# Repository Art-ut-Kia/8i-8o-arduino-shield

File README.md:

# 8i-8o-arduino-shield
Arduino Schield / Reads 8 push-button switches &amp; Drives 8 LED's

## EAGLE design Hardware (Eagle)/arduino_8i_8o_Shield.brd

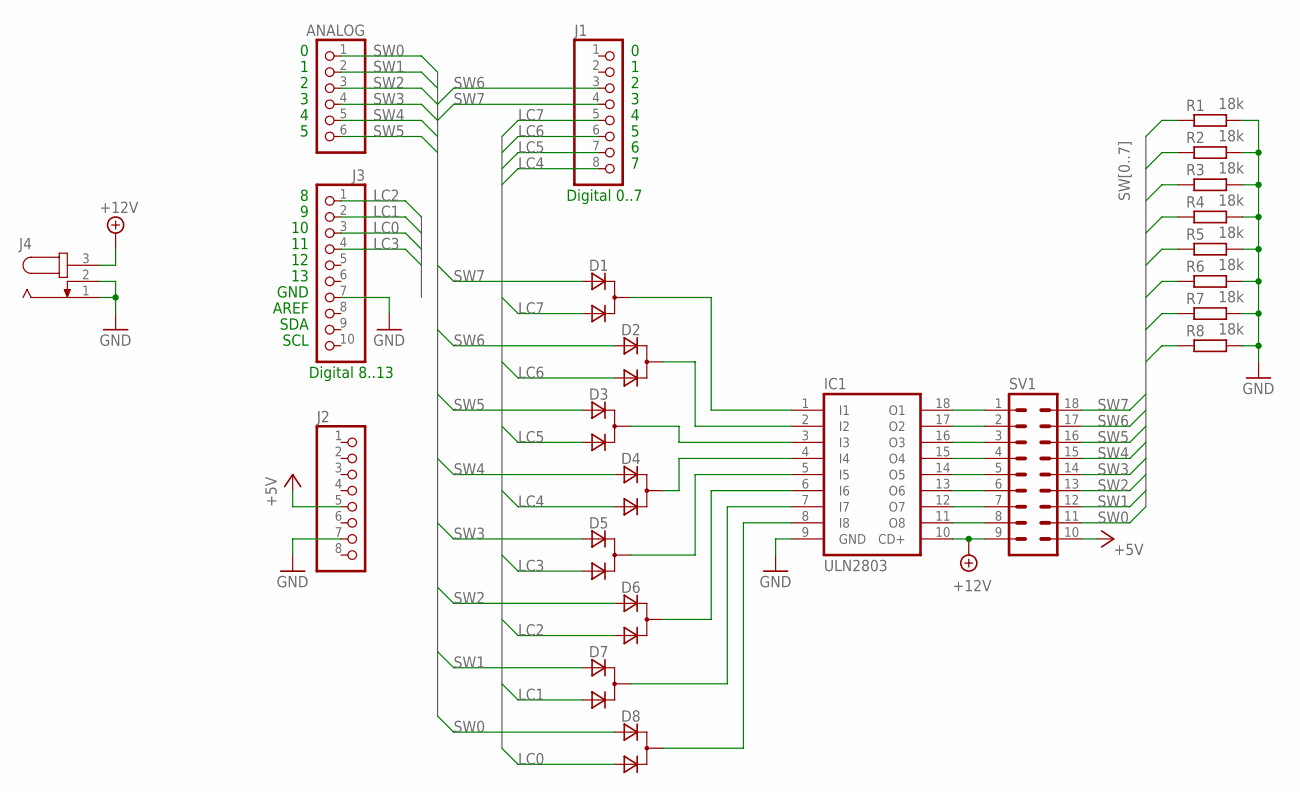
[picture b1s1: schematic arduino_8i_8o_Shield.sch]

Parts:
ANALOG: PINHD-1X6; 1X06
D1, D2, D3, D4, D5, D6, D7, D8: VAR2_SOT23; SOT-23
IC1: ULN2803; DIL18
J1, J2: PINHD-1X8TH; 1X08-TH
J3: PINHD-1X10TH; 1X10-TH
J4: JACK-PLUG0; SPC4077
R1, R2, R3, R4, R5, R6, R7, R8: 18k; M1206
SV1: IC18PL

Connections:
+5V: J2.5, SV1.10
+12V: IC1.10 (CD+), J4.3, SV1.9
GND: IC1.9 (GND), J2.7, J3.7, J4.1, J4.2, R1.2, R2.2, R3.2, R4.2, R5.2, R6.2, R7.2, R8.2
LC0: D8.3 (A2), J3.3
LC1: D7.3 (A2), J3.2
LC2: D6.3 (A2), J3.1
LC3: D5.3 (A2), J3.4
LC4: D4.3 (A2), J1.8
LC5: D3.3 (A2), J1.7
LC6: D2.3 (A2), J1.6
LC7: D1.3 (A2), J1.5
unnamed: IC1.11 (O8), SV1.8
unnamed: IC1.18 (O1), SV1.1
unnamed: IC1.17 (O2), SV1.2
unnamed: IC1.16 (O3), SV1.3
unnamed: IC1.15 (O4), SV1.4
unnamed: IC1.14 (O5), SV1.5
unnamed: IC1.13 (O6), SV1.6
unnamed: IC1.12 (O7), SV1.7
unnamed: D1.1 (C), IC1.1 (I1)
unnamed: D2.1 (C), IC1.2 (I2)
unnamed: D3.1 (C), IC1.3 (I3)
unnamed: D4.1 (C), IC1.4 (I4)
unnamed: D5.1 (C), IC1.5 (I5)
unnamed: D6.1 (C), IC1.6 (I6)
unnamed: D7.1 (C), IC1.7 (I7)
unnamed: D8.1 (C), IC1.8 (I8)
SW0: ANALOG.1, D8.2 (A1), R1.1, SV1.11
SW1: ANALOG.2, D7.2 (A1), R2.1, SV1.12
SW2: ANALOG.3, D6.2 (A1), R3.1, SV1.13
SW3: ANALOG.4, D5.2 (A1), R4.1, SV1.14
SW4: ANALOG.5, D4.2 (A1), R5.1, SV1.15
SW5: ANALOG.6, D3.2 (A1), R6.1, SV1.16
SW6: D2.2 (A1), J1.3, R7.1, SV1.17
SW7: D1.2 (A1), J1.4, R8.1, SV1.18

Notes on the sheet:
Digital 0..7
Digital 8..13
GND
AREF
SDA
SCL

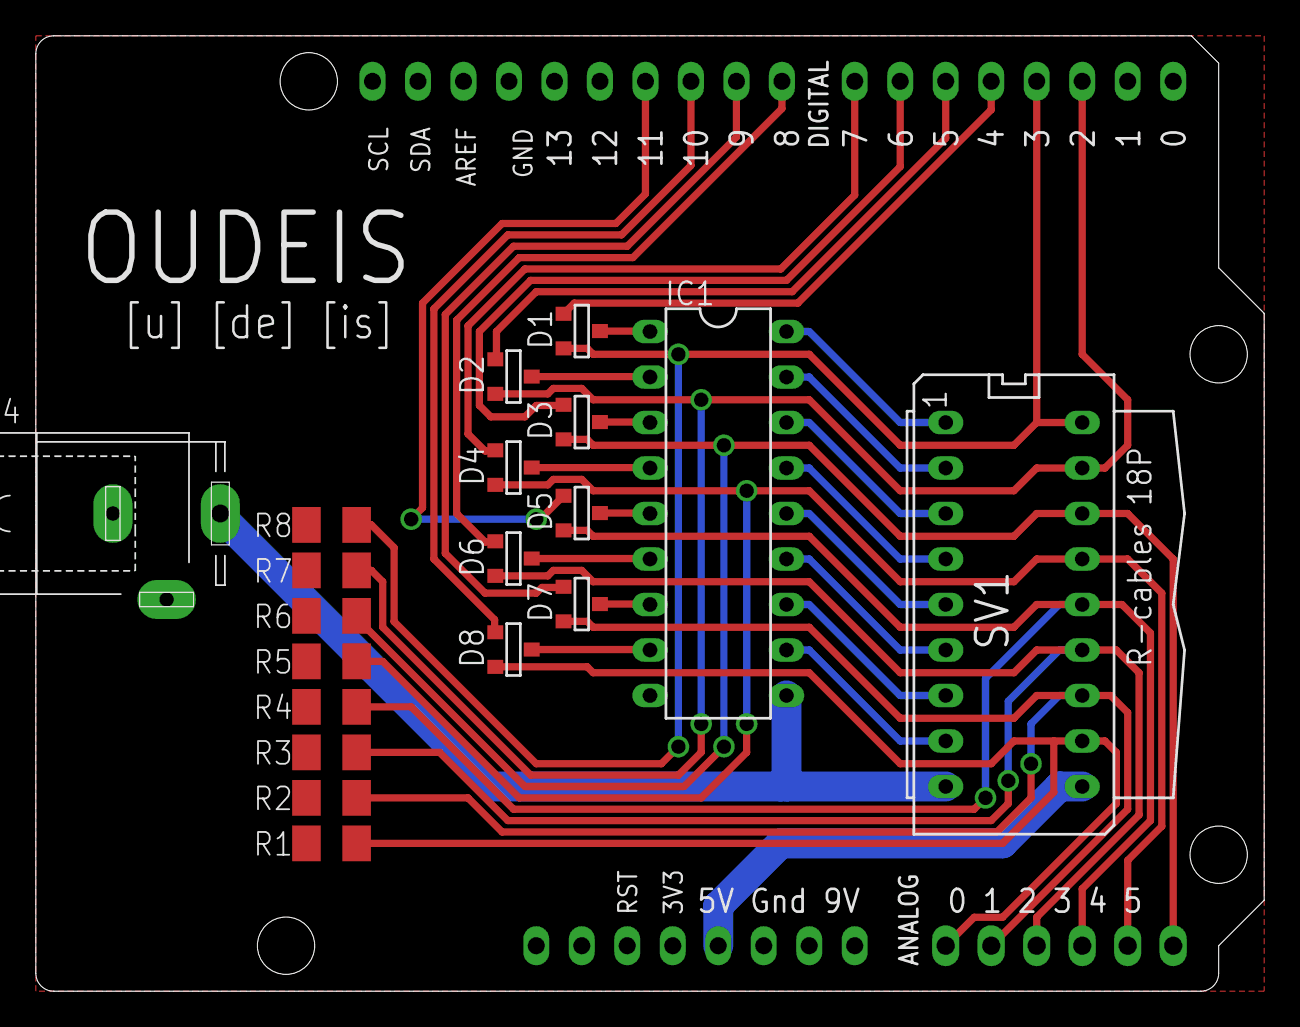
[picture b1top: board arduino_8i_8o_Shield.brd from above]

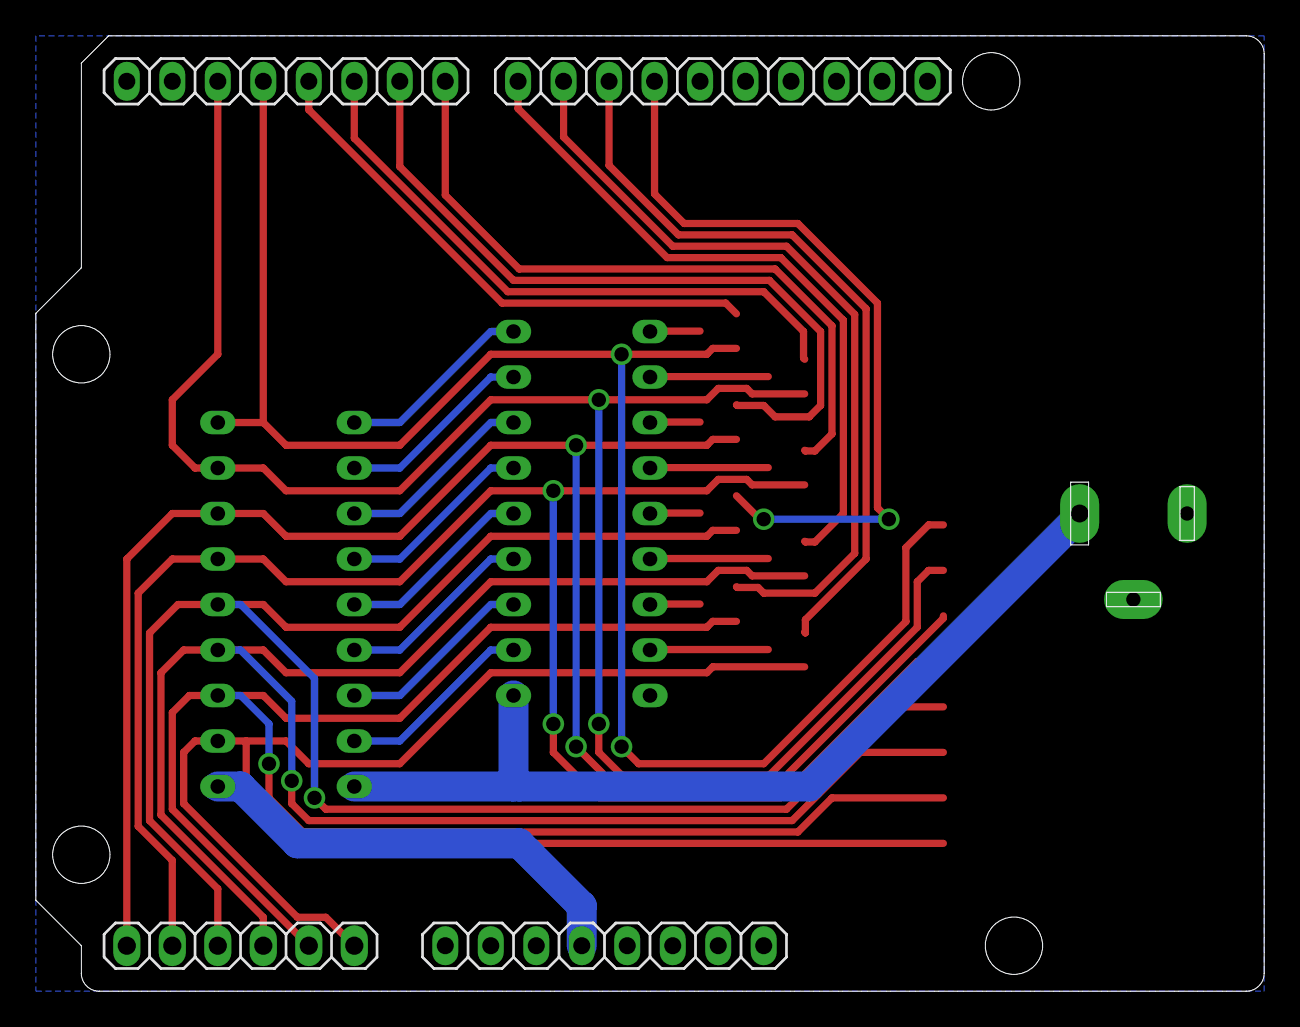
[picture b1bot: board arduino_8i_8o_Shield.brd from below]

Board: 2 copper layers, 68.6 x 53.3 mm, 23 parts (4 on the bottom side), 35 nets.

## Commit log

2015-10-04 Added Eagle Files + a Picture of 3 freshly assembled boards
    This arduino shield reads 8 push-button switches and controls 8 LED's
2015-10-04 Revert "Added Eagle Files + a Picture of 3 freshly assembled boards"
    This reverts commit d92fc356f843c7ef5f3d70934b7907950014cf2e.
2015-10-04 Revert "Revert "Added Eagle Files + a Picture of 3 freshly assembled boards""
    This reverts commit cff66f8e90e7c38e4805cda6485667aeac220695.
2015-10-08 Added 8 x 18k pull-down resistors on switches inputs
    The absence of these resistors induced a cross talk between LED output
    and switches reading inputs
2015-10-08 Reajusted the logo position ; Added a screen copy of the board design
    Cosmetic changes
2015-10-09 Added a binary version of arduino sketch
    This version of sketch transmits an octet at any change in the 8
    switches statuses (one switch status per bit). In the same way, all 8 x
    LEDs are commanded simultaneously by a single octet.
2015-10-17 Changed files into hard links
